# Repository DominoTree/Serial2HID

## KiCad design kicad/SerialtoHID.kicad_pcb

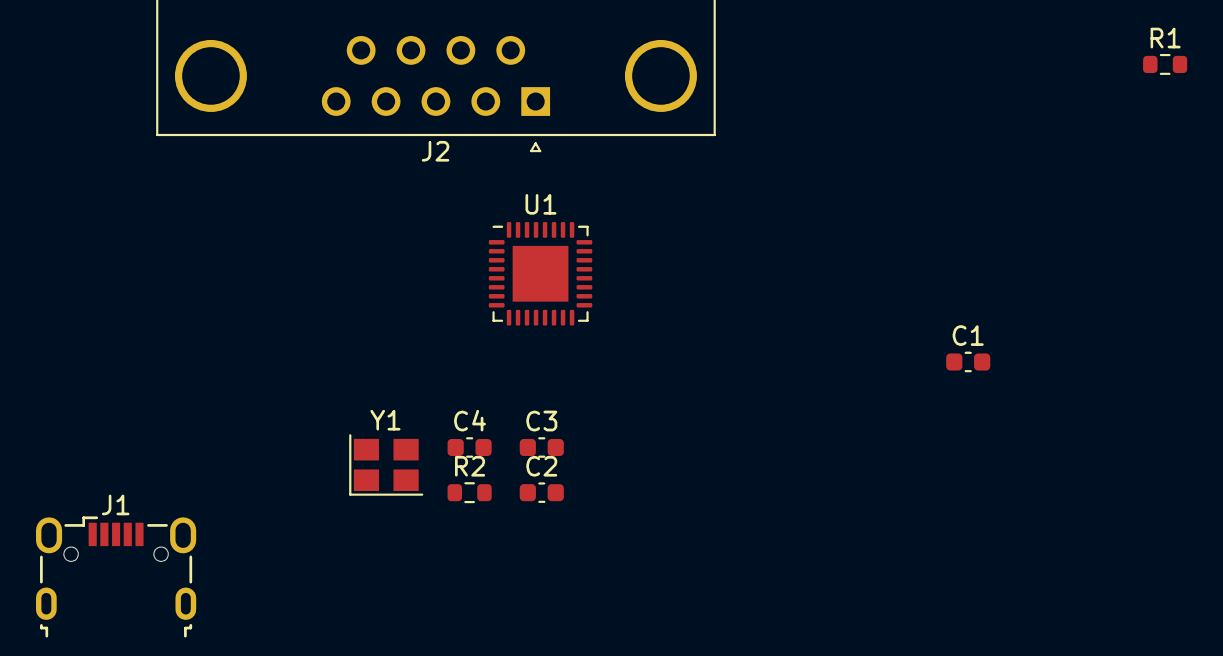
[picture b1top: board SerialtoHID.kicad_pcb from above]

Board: 2 copper layers, 10 parts (0 on the bottom side), 9 nets, no tracks yet.

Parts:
C1, C2: 22pF; C_0603_1608Metric
C3: 1uF; C_0603_1608Metric
C4: 0.1uF; C_0603_1608Metric
J1: USB_B; USB_Micro-B_Wuerth_629105150521
J2: DB9_Male_MountingHoles; DSUB-9_Male_Horizontal_P2.77x2.84mm_EdgePinOffset7.70mm_Hou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
R1, R2: 10k; R_0603_1608Metric
U1: ATmega32U2-M; QFN-32-1EP_5x5mm_P0.5mm_EP3.1x3.1mm
Y1: 16MHz; Crystal_SMD_3225-4Pin_3.2x2.5mm

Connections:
/MOUSE_TX: J2.3, R2.1, U1.8 (PD2)
/~RESET: R1.1, U1.24 (PC1/~RESET)
GND: C1.1, C2.1, C3.1, C4.2, J1.4 (GND), J1.5 (Shield), J2.0 (PAD), J2.5, U1.3 (GND), U1.28 (UGND), U1.33 (GND), Y1.2, Y1.3
unnamed: C1.2, U1.1 (XTAL1), Y1.4
unnamed: C2.2, U1.2 (PC0/XTAL2), Y1.1
unnamed: C3.2, U1.27 (UCAP)
unnamed: J1.2 (D-), U1.30 (D-)
unnamed: J1.3 (D+), U1.29 (D+)
VCC: C4.1, J1.1 (VBUS), J2.7, R1.2, R2.2, U1.4 (VCC), U1.31 (UVCC), U1.32 (AVCC)

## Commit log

2021-04-24 init
